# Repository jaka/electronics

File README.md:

# KiCad electronic projects repository

I like to solder, but information I find are scattered everywhere or incomplete. Here I collect schematics and PCBs.

Most of schematics came from datasheets or application notes. All PCBs were drawn by me.

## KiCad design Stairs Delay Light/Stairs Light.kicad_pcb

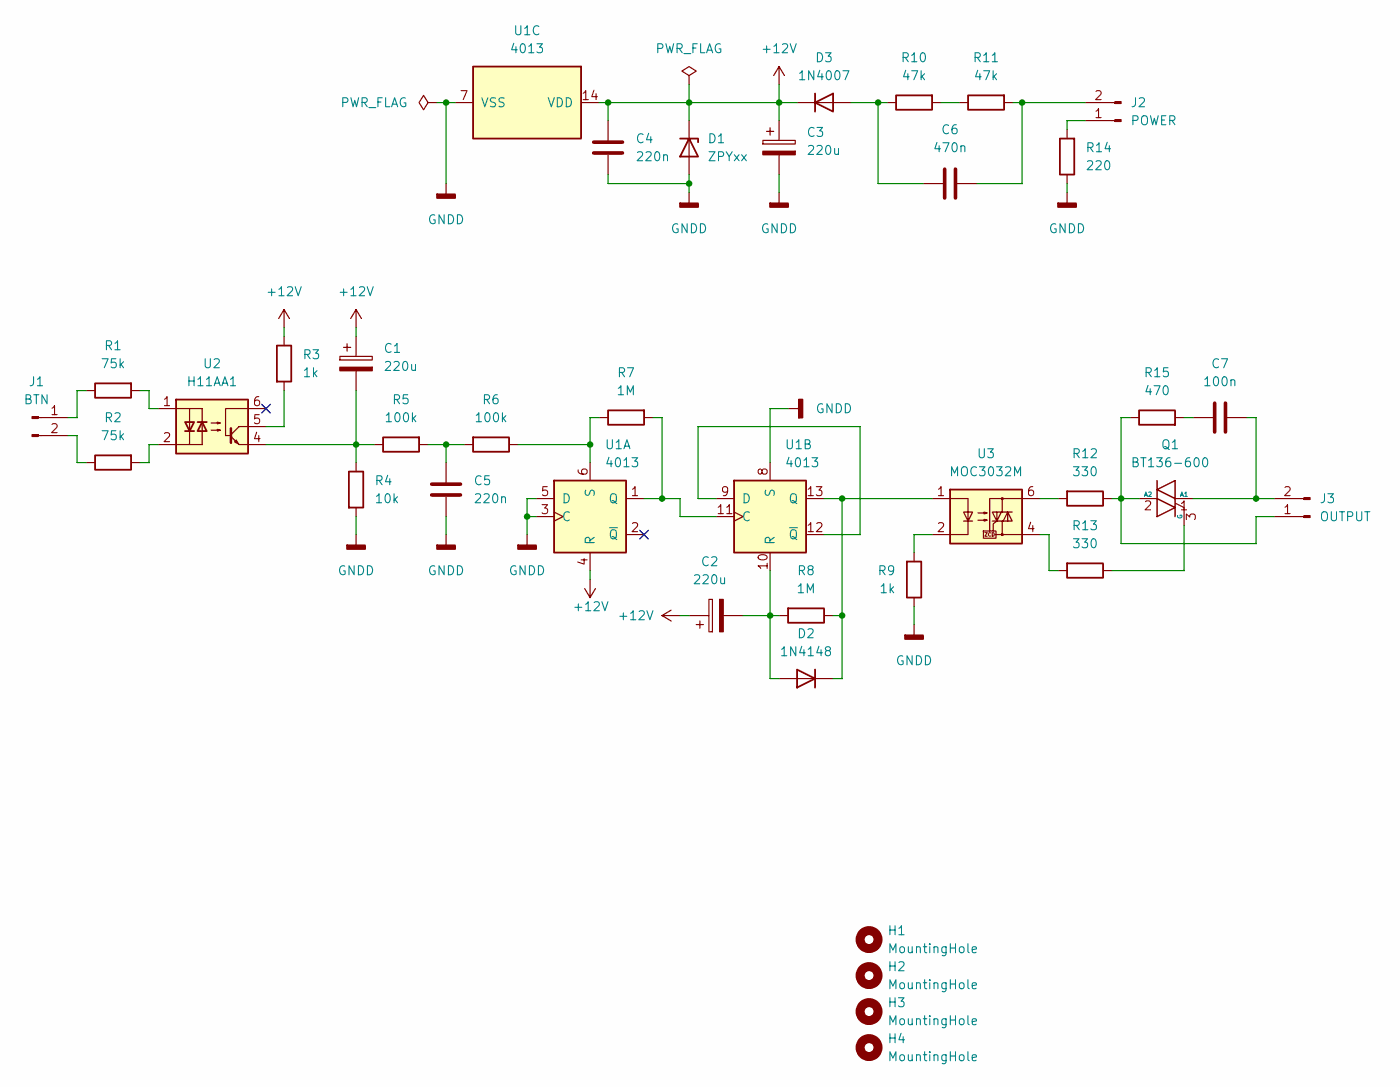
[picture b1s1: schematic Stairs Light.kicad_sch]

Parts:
C1, C2, C3: 220u; CP_Radial_D8.0mm_P3.50mm
C4, C5: 220n; C_Rect_L7.0mm_W3.5mm_P2.50mm_P5.00mm
C6: 470n; C_Rect_L24.0mm_W7.0mm_P22.50mm_MKT
C7: 100n; C_Rect_L24.0mm_W7.0mm_P22.50mm_MKT
D1: ZPYxx; D_DO-41_SOD81_P10.16mm_Horizontal
D2: 1N4148; D_DO-35_SOD27_P7.62mm_Horizontal
D3: 1N4007; D_DO-41_SOD81_P10.16mm_Horizontal
H1, H2, H3, H4: MountingHole; MountingHole_4.3mm_M4
J1: BTN; PhoenixContact_MSTBA_2,5_2-G-5,08_1x02_P5.08mm_Horizontal
J2: POWER; PhoenixContact_MSTBA_2,5_2-G-5,08_1x02_P5.08mm_Horizontal
J3: OUTPUT; PhoenixContact_MSTBA_2,5_2-G-5,08_1x02_P5.08mm_Horizontal
Q1: BT136-600; TO-220-3_Vertical
R1, R2: 75k; R_Axial_DIN0207_L6.3mm_D2.5mm_P10.16mm_Horizontal
R3, R9: 1k; R_Axial_DIN0207_L6.3mm_D2.5mm_P10.16mm_Horizontal
R4: 10k; R_Axial_DIN0207_L6.3mm_D2.5mm_P10.16mm_Horizontal
R5, R6: 100k; R_Axial_DIN0207_L6.3mm_D2.5mm_P10.16mm_Horizontal
R7, R8: 1M; R_Axial_DIN0207_L6.3mm_D2.5mm_P10.16mm_Horizontal
R10, R11: 47k; R_Axial_DIN0207_L6.3mm_D2.5mm_P10.16mm_Horizontal
R12, R13: 330; R_Axial_DIN0207_L6.3mm_D2.5mm_P10.16mm_Horizontal
R14: 220; R_Axial_DIN0309_L9.0mm_D3.2mm_P12.70mm_Horizontal
R15: 470; R_Axial_DIN0309_L9.0mm_D3.2mm_P12.70mm_Horizontal
U1: 4013; DIP-14_W7.62mm_Socket
U2: H11AA1; DIP-6_W7.62mm_LongPads
U3: MOC3032M; DIP-6_W7.62mm_LongPads

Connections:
+12V: C1.1, C2.1, C3.1, C4.1, D1.1 (K), D3.1 (K), R3.1, U1.4 (R), U1.14 (VDD)
GNDD: C3.2, C4.2, C5.2, D1.2 (A), R4.2, R9.1, R14.1, U1.3 (C), U1.5 (D), U1.7 (VSS), U1.8 (S)
unnamed: C1.2, R4.1, R5.1, U2.4
unnamed: C2.2, D2.2 (A), R8.2, U1.10 (R)
unnamed: C5.1, R5.2, R6.2
unnamed: C6.1, D3.2 (A), R10.1
unnamed: C6.2, J2.2, R11.2
unnamed: C7.1, J3.2, Q1.1 (A1)
unnamed: C7.2, R15.2
unnamed: D2.1 (K), R8.1, U1.13 (Q), U3.1
unnamed: J1.1, R1.1
unnamed: J1.2, R2.1
unnamed: J2.1, R14.2
unnamed: J3.1, Q1.2 (A2), R12.1, R15.1
unnamed: Q1.3 (G), R13.1
unnamed: R1.2, U2.1
unnamed: R2.2, U2.2
unnamed: R3.2, U2.5
unnamed: R6.1, R7.1, U1.6 (S)
unnamed: R7.2, U1.1 (Q), U1.11 (C)
unnamed: R9.2, U3.2
unnamed: R10.2, R11.1
unnamed: R12.2, U3.6
unnamed: R13.2, U3.4
unnamed: U1.9 (D), U1.12 (~Q)

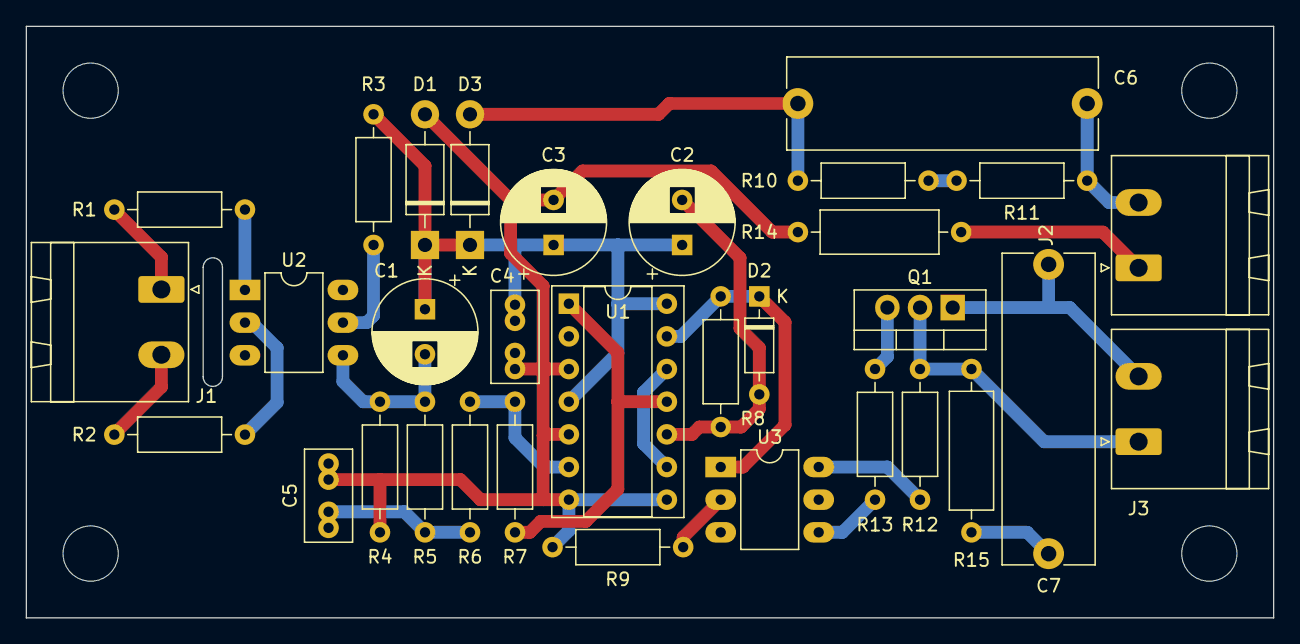
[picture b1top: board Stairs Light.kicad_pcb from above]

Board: 2 copper layers, 97.0 x 46.0 mm, 36 parts (0 on the bottom side), 25 nets.

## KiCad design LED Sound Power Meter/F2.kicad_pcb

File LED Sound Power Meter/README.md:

# LED Sound Power Meter

* EDA: **Kicad 6.0.11**
* PCB dimensions: **100 x 35 mm** (single sided)

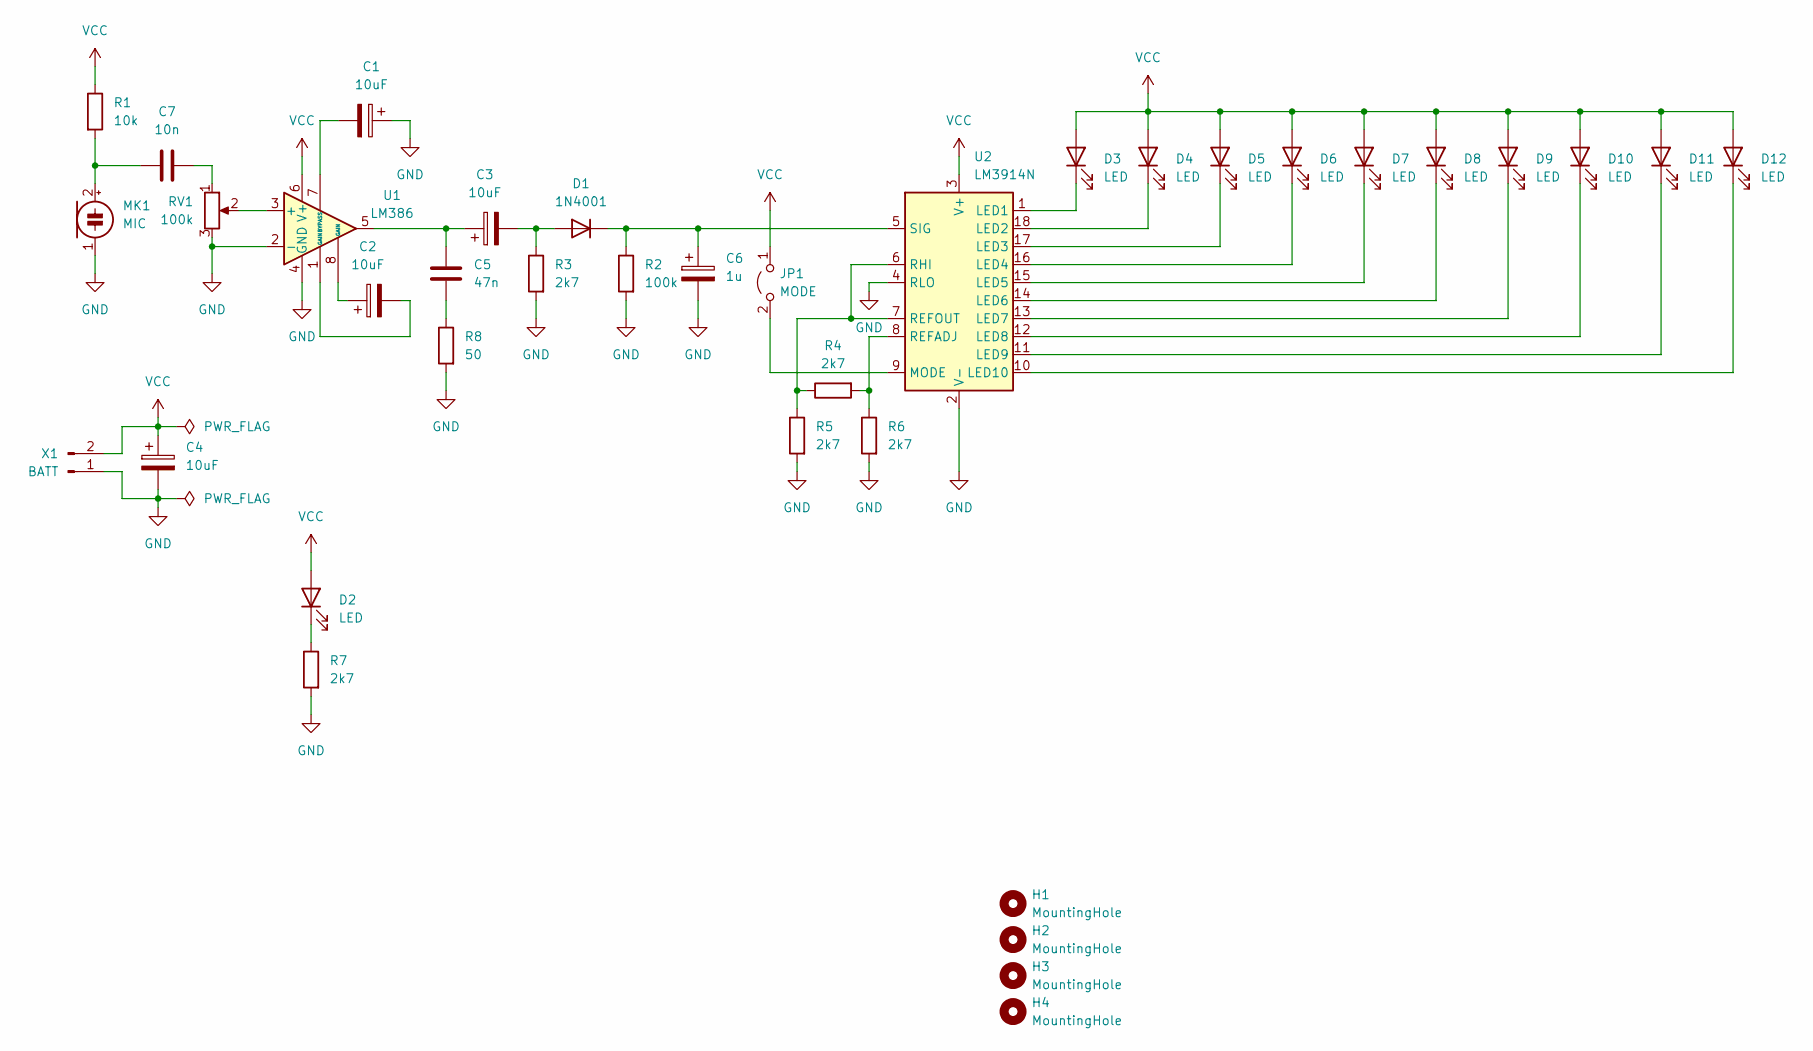
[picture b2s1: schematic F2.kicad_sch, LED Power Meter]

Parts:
C1, C2, C3, C4: 10uF; CP_Radial_D5.0mm_P2.00mm
C5: 47n; C_Rect_L7.0mm_W3.5mm_P2.50mm_P5.00mm
C6: 1u; CP_Radial_D5.0mm_P2.00mm
C7: 10n; C_Rect_L7.0mm_W3.5mm_P2.50mm_P5.00mm
D1: 1N4001; D_DO-41_SOD81_P10.16mm_Horizontal
D2, D3, D4, D5, D6, D7, D8, D9, D10, D11, D12: LED; LED_D5.0mm
H1, H2, H3, H4: MountingHole; MountingHole_3.2mm_M3
JP1: MODE; PinHeader_1x02_P2.54mm_Vertical
MK1: MIC; GMI9745P
R1: 10k; R_Axial_DIN0309_L9.0mm_D3.2mm_P12.70mm_Horizontal
R2: 100k; R_Axial_DIN0309_L9.0mm_D3.2mm_P12.70mm_Horizontal
R3, R4, R5, R6, R7: 2k7; R_Axial_DIN0309_L9.0mm_D3.2mm_P12.70mm_Horizontal
R8: 50; R_Axial_DIN0309_L9.0mm_D3.2mm_P12.70mm_Horizontal
RV1: 100k; Potentiometer_Piher_PT-10-V10_Vertical_Hole
U1: LM386; DIP-8_W7.62mm_LongPads
U2: LM3914N; DIP-18_W7.62mm_LongPads
X1: BATT; JST_PH_B2B-PH-K_1x02_P2.00mm_Vertical

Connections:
GND: C1.1, C4.2, C6.2, MK1.1 (-), R2.2, R3.2, R5.2, R6.2, R7.2, R8.2, RV1.3, U1.2 (-), U1.4 (GND), U2.2 (V-), U2.4 (RLO), X1.1
unnamed: C1.2, U1.7 (BYPASS)
unnamed: C2.1, U1.8 (GAIN)
unnamed: C2.2, U1.1 (GAIN)
unnamed: C3.1, C5.1, U1.5
unnamed: C3.2, D1.2 (A), R3.1
unnamed: C5.2, R8.1
unnamed: C6.1, D1.1 (K), R2.1, U2.5 (SIG)
unnamed: C7.1, MK1.2 (+), R1.2
unnamed: C7.2, RV1.1
unnamed: D2.1 (K), R7.1
unnamed: D3.1 (K), U2.1 (LED1)
unnamed: D4.1 (K), U2.18 (LED2)
unnamed: D5.1 (K), U2.17 (LED3)
unnamed: D6.1 (K), U2.16 (LED4)
unnamed: D7.1 (K), U2.15 (LED5)
unnamed: D8.1 (K), U2.14 (LED6)
unnamed: D9.1 (K), U2.13 (LED7)
unnamed: D10.1 (K), U2.12 (LED8)
unnamed: D11.1 (K), U2.11 (LED9)
unnamed: D12.1 (K), U2.10 (LED10)
unnamed: JP1.2 (B), U2.9 (MODE)
unnamed: R4.1, R5.1, U2.6 (RHI), U2.7 (REFOUT)
unnamed: R4.2, R6.1, U2.8 (REFADJ)
unnamed: RV1.2, U1.3 (+)
VCC: C4.1, D2.2 (A), D3.2 (A), D4.2 (A), D5.2 (A), D6.2 (A), D7.2 (A), D8.2 (A), D9.2 (A), D10.2 (A), D11.2 (A), D12.2 (A), JP1.1 (A), R1.1, U1.6 (V+), U2.3 (V+), X1.2

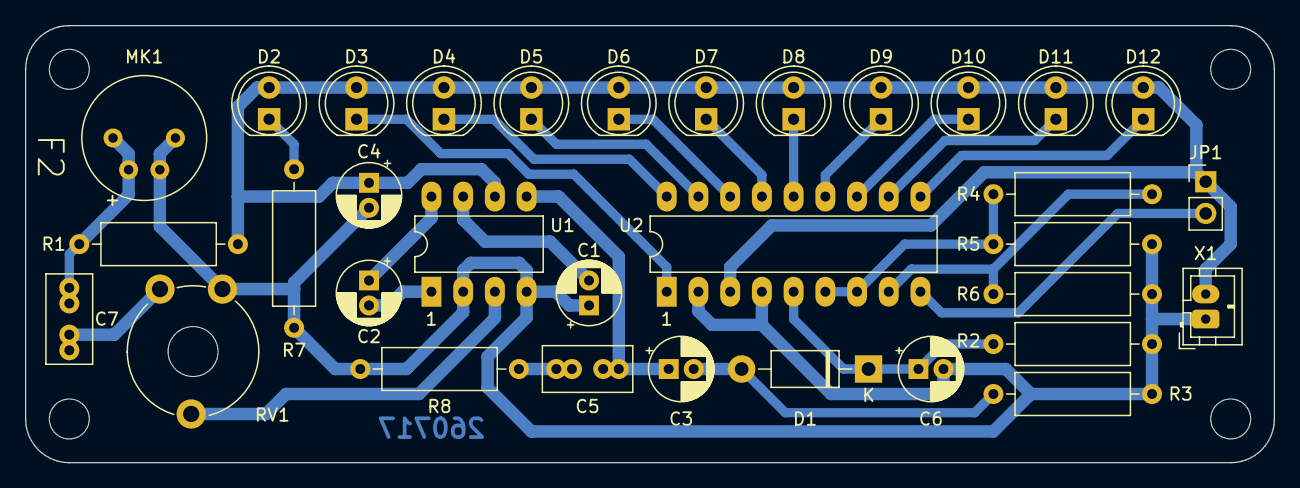
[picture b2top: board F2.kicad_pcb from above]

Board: 2 copper layers, 100.0 x 35.0 mm, 37 parts (0 on the bottom side), 26 nets.

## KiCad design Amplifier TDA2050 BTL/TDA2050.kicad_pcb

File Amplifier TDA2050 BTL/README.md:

# TDA2050 DIY Audio Power Amplifier Circuit

This is circuit combines two TDA2050 audio amplifier integrated circuits for so-called bridge-tied load where each speaker input is connected to amplifier output. Dual voltage power supply is needed.

* EDA: **Kicad 6.0.11**
* PCB dimensions: **74 x 39 mm** (single sided)

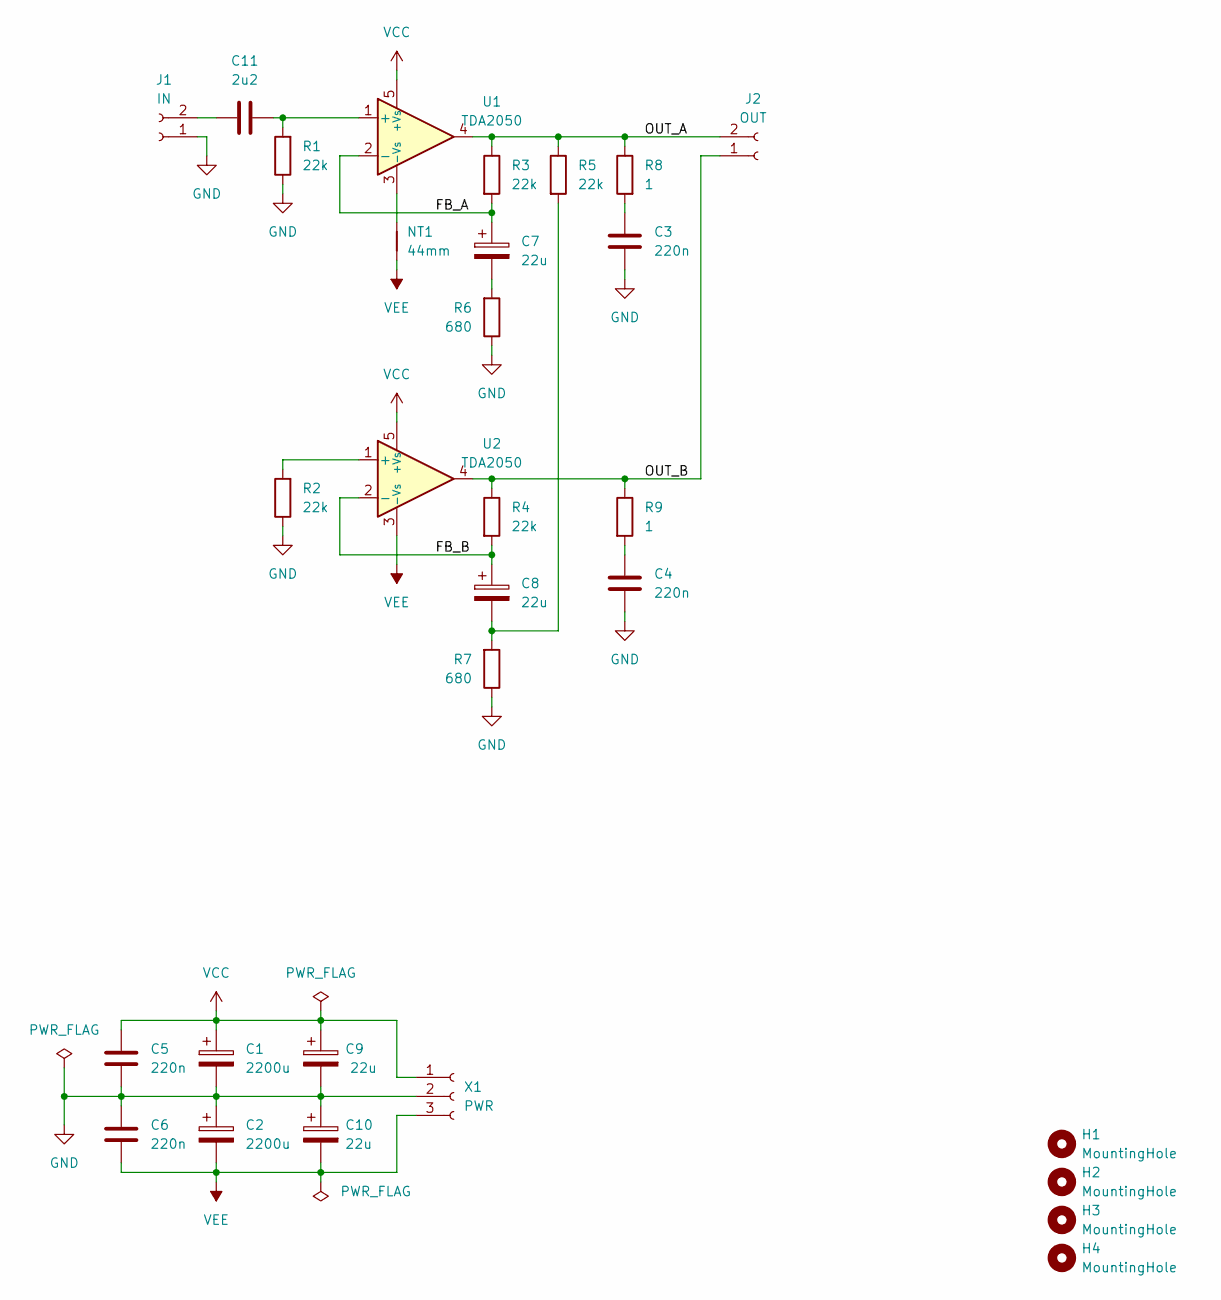
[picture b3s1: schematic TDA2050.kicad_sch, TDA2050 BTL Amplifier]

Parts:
C1, C2: 2200u; CP_Radial_D10.0mm_P5.00mm_P7.50mm
C3, C4, C5, C6: 220n; C_Rect_L7.0mm_W3.5mm_P2.50mm_P5.00mm
C7, C8, C9, C10: 22u; CP_Radial_D6.3mm_P2.50mm
C11: 2u2; C_Radial_D5.0mm_H7.0mm_P2.00mm
H1, H2, H3, H4: MountingHole; MountingHole_4.3mm_M4
J1: IN; JST_PH_B2B-PH-K_1x02_P2.00mm_Vertical
J2: OUT; JST_VH_B2P-VH_1x02_P3.96mm_Vertical
NT1: 44mm; Wire44mm
R1, R2, R3, R4, R5: 22k; R_Axial_DIN0207_L6.3mm_D2.5mm_P10.16mm_Horizontal
R6, R7: 680; R_Axial_DIN0207_L6.3mm_D2.5mm_P10.16mm_Horizontal
R8, R9: 1; R_Axial_DIN0309_L9.0mm_D3.2mm_P5.08mm_Vertical
U1, U2: TDA2050; TO-220-5_P3.4x3.7mm_StaggerOdd_Lead3.8mm_Vertical
X1: PWR; JST_VH_B3P-VH_1x03_P3.96mm_Vertical

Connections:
/FB_A: C7.1, R3.2, U1.2 (-)
/FB_B: C8.1, R4.2, U2.2 (-)
/OUT_A: J2.2, R3.1, R5.1, R8.1, U1.4
/OUT_B: J2.1, R4.1, R9.1, U2.4
GND: C1.2, C2.1, C3.2, C4.2, C5.2, C6.1, C9.2, C10.1, J1.1, R1.1, R2.1, R6.1, R7.1, X1.2
unnamed: C7.2, R6.2
unnamed: C8.2, R5.2, R7.2
unnamed: C11.1, J1.2
unnamed: C11.2, R1.2, U1.1 (+)
unnamed: R2.2, U2.1 (+)
unnamed: C3.1, R8.2
unnamed: C4.1, R9.2
unnamed: NT1.2, U1.3 (-Vs)
VCC: C1.1, C5.1, C9.1, U1.5 (+Vs), U2.5 (+Vs), X1.1
VEE: C2.2, C6.2, C10.2, NT1.1, U2.3 (-Vs), X1.3

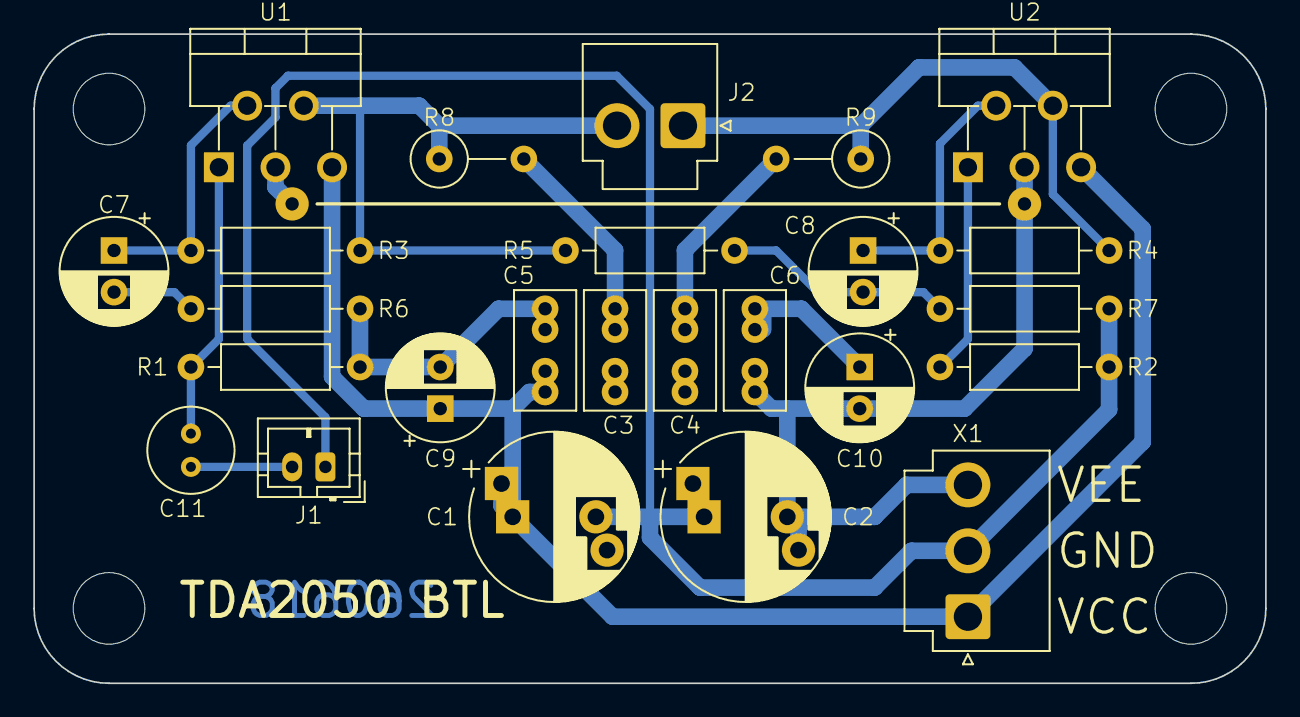
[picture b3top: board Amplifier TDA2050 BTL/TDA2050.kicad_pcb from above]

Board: 2 copper layers, 74.0 x 39.0 mm, 30 parts (0 on the bottom side), 15 nets.

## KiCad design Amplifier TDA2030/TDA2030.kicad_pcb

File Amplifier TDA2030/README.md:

# TDA2030 DIY Audio Power Amplifier Circuit

This is a simple class AB audio amplifier built around the TDA2030 audio amplifier integrated circuit. It’s a classic beginner-friendly design often used for small speakers, desktop audio, or homemade powered speakers, where only one power supply voltage is available.

* EDA: **Kicad 6.0.11**
* PCB dimensions: **61 x 34 mm** (single sided)

Circuit is versatile: it can also accomodate TDA2030A, TDA2050 and LM1875 due to same pinout, but in all cases heat sink for IC is mandatory!

# Expected performance

| Supply Voltage | Speaker | Approx. Power |
|---|---|---|
| 12V | 8Ω | 6–8W |
| 18V | 4Ω | 14–18W |

## Power supply
- 12 V–18 V regulated DC supply
- 2 A or more

## When built

Before connecting the loudspeaker and input source, measure (bias) voltage at test point TP1. The voltage here should be a half of supply voltage. If it's not, check both resistors R₁ and R₂ or replace C₁. Capacitor may have too low resistance and some current is flowing through, resulting in bias voltage drop. The same voltage should be at test point TP2 just before output DC decoupling capacitor.

| Component | Recommended value | Purpose | Larger than recommended value | Smaller than recommended value |
|-----------|------------------|---------|------------------------------|-------------------------------|
| R₁/R₂ | 100 kΩ | Bias voltage divider | Poor high-frequency attenuation | Danger of oscillation |
| R₃ | 100 kΩ | Non-inverting input biasing | Increase of input impedance | Decrease in input impedance |
| R₄ | 4,7kΩ | Closed loop gain setting | Decrease of gain | Increase in gain |
| R₅ | 100 kΩ | Closed loop gain setting | Increase of gain | Decrease in gain |
| R₆ | 1 Ω | Frequency stability | Danger of oscillation at high frequencies with inductive loads | — |
| R₇ | 2 kΩ | Upper frequency cutoff | Poor high-frequency attenuation | — |
| C₁ | 10 µF | Bias voltage stabilizing | | |
| C₂ | 2,2 µF | Input DC decoupling | — | Increase in low-frequency cutoff |
| C₃ | 2,2 µF | Inverting input DC decoupling | — | Increase in low-frequency cutoff |
| C₄ | 220 µF | Supply voltage bypass | — | Danger of oscillation |
| C₅ | 0,22 µF | Supply voltage bypass | — | Danger of oscillation |
| C₆ | 0,22 µF | Frequency stability | — | Danger of oscillation |
| C₇ | 1 / (2πBR₅) | Upper frequency cutoff | Smaller bandwidth | Larger bandwidth |
| C₈ | 2200 µF | Output DC decoupling | — | Increase in low-frequency cutoff |
| D₁, D₂ | 1N4001 | To protect the device against output voltage spikes | — | — |

These values are from ST TDA2030A datasheet. ST does not produce this IC anymore, but there are many others producers. Check theirs datasheet for recommended values.

Closed loop gain must be higher than 24 dB.

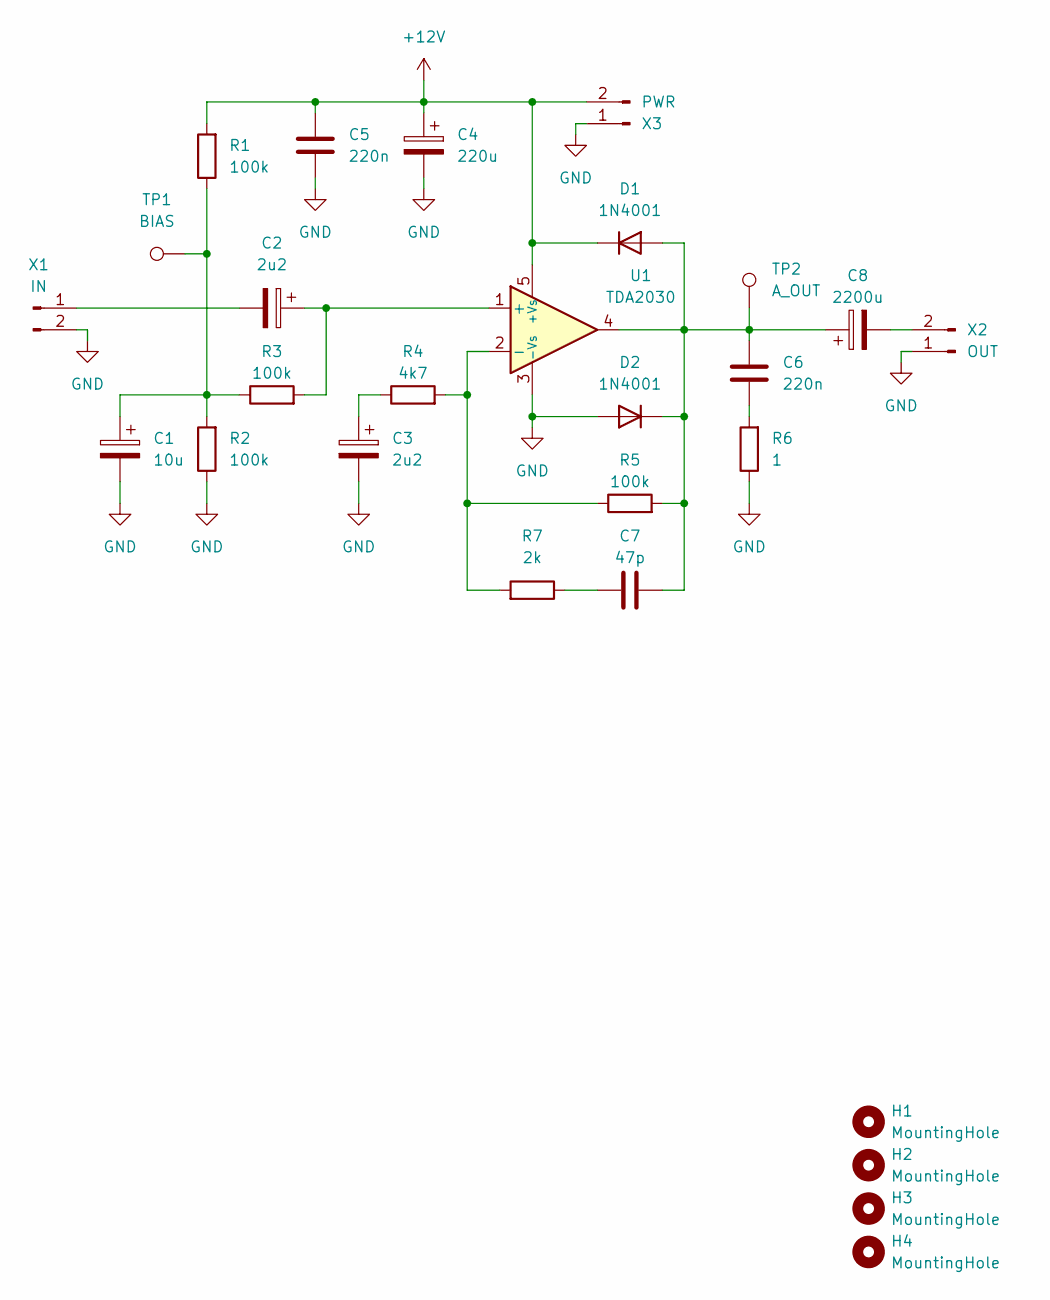
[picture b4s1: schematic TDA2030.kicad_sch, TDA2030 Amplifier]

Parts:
C1: 10u; CP_Radial_D5.0mm_P2.50mm
C2, C3: 2u2; CP_Radial_D5.0mm_P2.50mm
C4: 220u; CP_Radial_D10.0mm_P2.50mm_P5.00mm
C5, C6: 220n; C_Rect_L7.0mm_W3.5mm_P2.50mm_P5.00mm
C7: 47p; C_Rect_L7.0mm_W3.5mm_P2.50mm_P5.00mm
C8: 2200u; CP_Radial_D10.0mm_P5.00mm_P7.50mm
D1, D2: 1N4001; D_DO-41_SOD81_P10.16mm_Horizontal
H1, H2, H3, H4: MountingHole; MountingHole_3.2mm_M3
R1, R2, R3, R5: 100k; R_Axial_DIN0309_L9.0mm_D3.2mm_P12.70mm_Horizontal
R4: 4k7; R_Axial_DIN0309_L9.0mm_D3.2mm_P12.70mm_Horizontal
R6: 1; R_Axial_DIN0411_L9.9mm_D3.6mm_P5.08mm_Vertical
R7: 2k; R_Axial_DIN0309_L9.0mm_D3.2mm_P12.70mm_Horizontal
TP1: BIAS; TestPoint_Pad_D2.5mm
TP2: A_OUT; TestPoint_Pad_D2.5mm
U1: TDA2030; TO-220-5_P3.4x3.7mm_StaggerOdd_Lead3.8mm_Vertical
X1: IN; JST_PH_B2B-PH-K_1x02_P2.00mm_Vertical
X2: OUT; JST_VH_B2P-VH-B_1x02_P3.96mm_Vertical
X3: PWR; JST_VH_B2P-VH-B_1x02_P3.96mm_Vertical

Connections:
+12V: C4.1, C5.1, D1.1 (K), R1.2, U1.5 (+Vs), X3.2
GND: C1.2, C3.2, C4.2, C5.2, D2.2 (A), R2.1, R6.1, U1.3 (-Vs), X1.2, X2.1, X3.1
unnamed: C1.1, R1.1, R2.2, R3.1, TP1.1
unnamed: C2.1, R3.2, U1.1 (+)
unnamed: C2.2, X1.1
unnamed: C3.1, R4.1
unnamed: C6.1, C7.2, C8.1, D1.2 (A), D2.1 (K), R5.2, TP2.1, U1.4
unnamed: C6.2, R6.2
unnamed: C7.1, R7.1
unnamed: C8.2, X2.2
unnamed: R4.2, R5.1, R7.2, U1.2 (-)

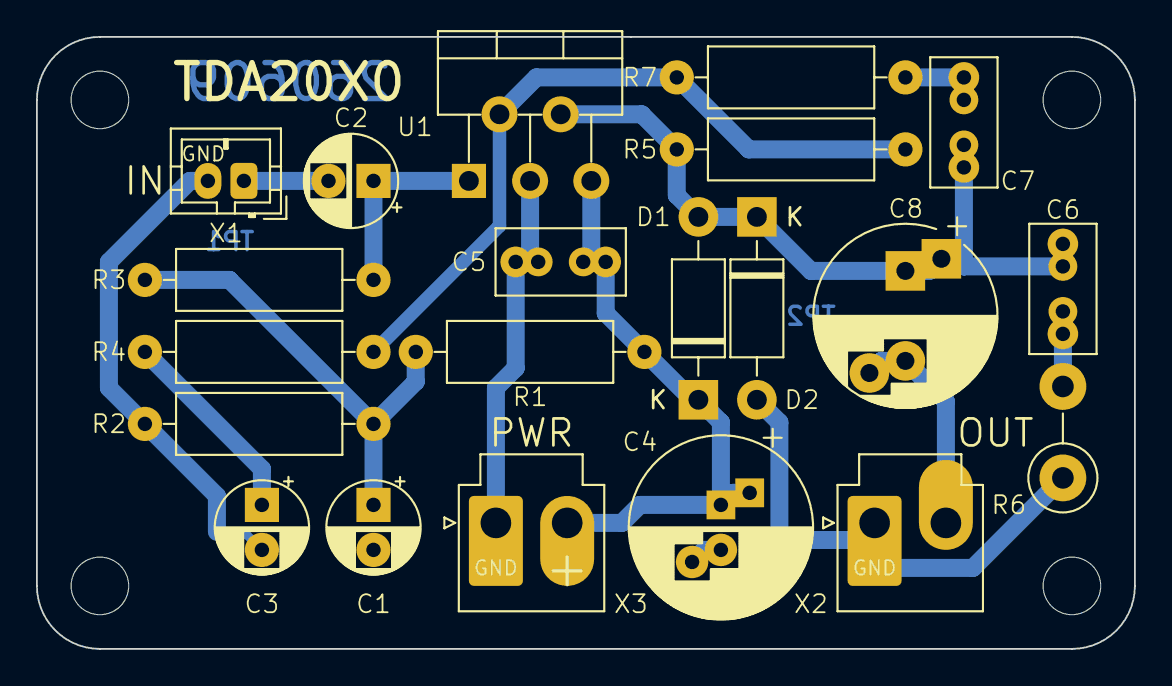
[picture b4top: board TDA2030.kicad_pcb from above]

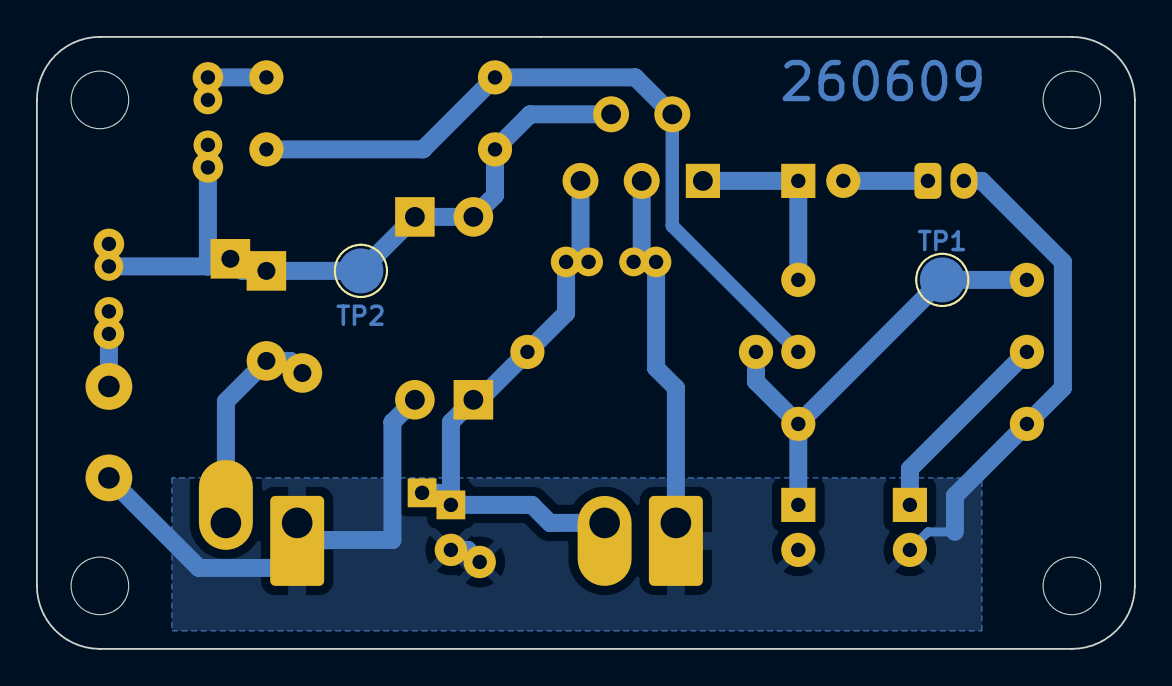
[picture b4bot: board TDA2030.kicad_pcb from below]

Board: 2 copper layers, 61.0 x 34.0 mm, 27 parts (2 on the bottom side), 11 nets.

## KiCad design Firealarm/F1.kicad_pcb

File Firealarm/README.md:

# Firealarm Tone Generator

This circuit simulates a fire alarm sound. When button SW1 is pressed, loudspeaker connected to terminal LS1 emits a tone that gradually rises in pitch and then holds steady at a constant pitch. The tone continues until the button is released. The pitch then drops again until the sound ceases completely. This process can be repeated indefinitely.

* EDA: **Kicad 6.0.11**
* PCB dimensions: **58 x 36 mm** (single sided)

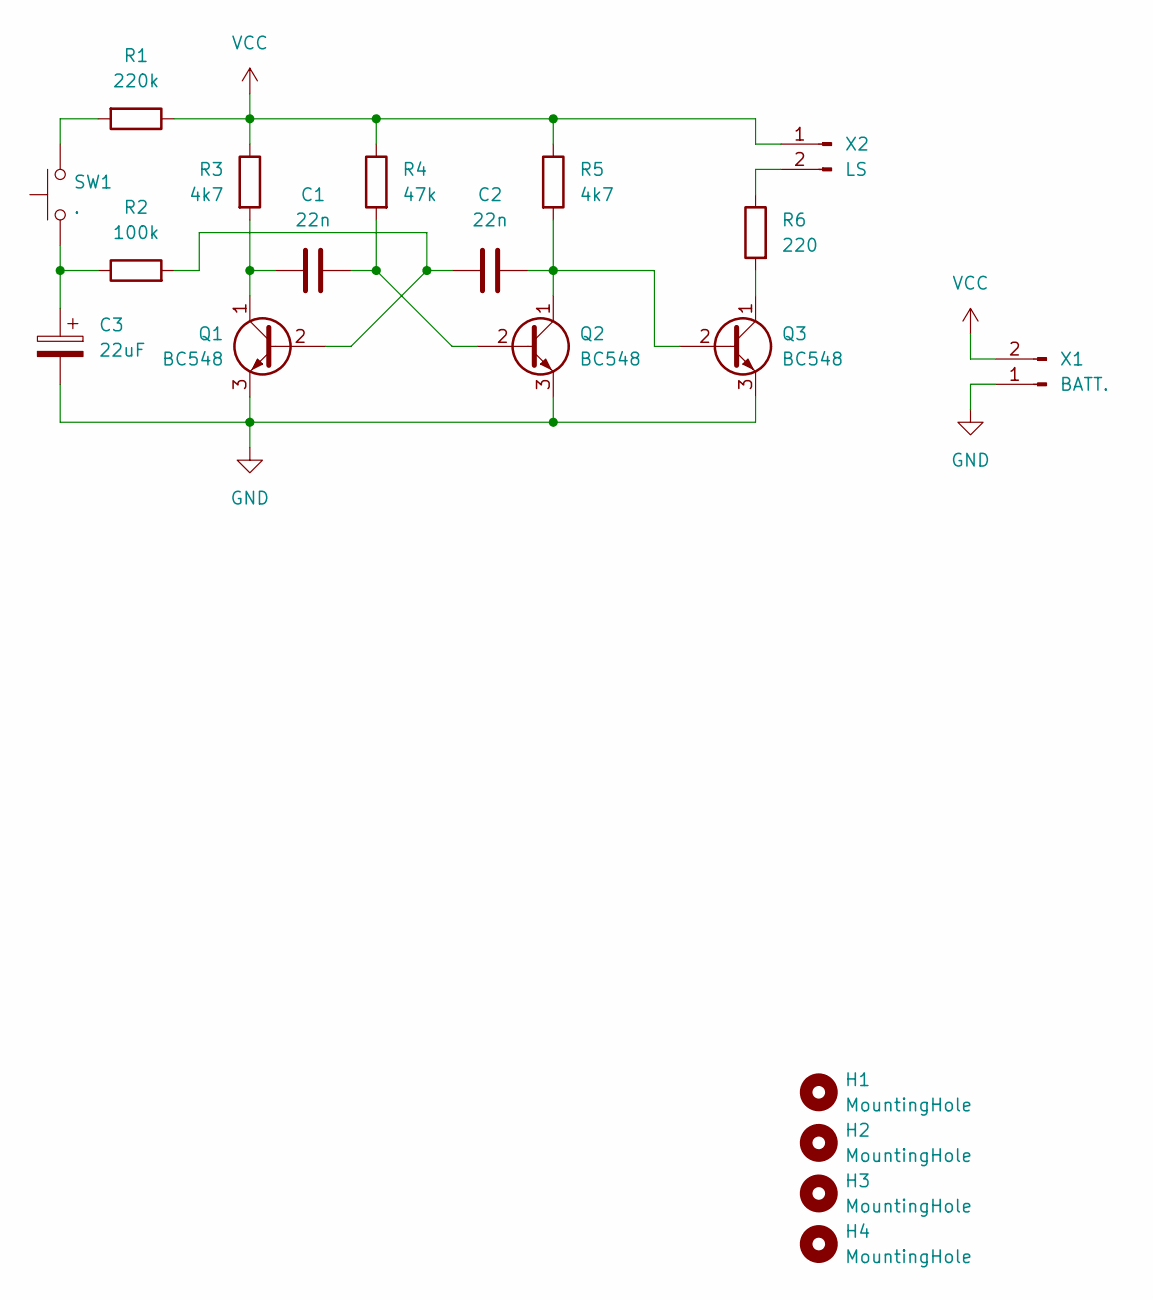
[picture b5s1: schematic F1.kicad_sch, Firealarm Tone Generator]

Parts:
C1, C2: 22n; C_Disc_D5.0mm_W2.5mm_P5.00mm
C3: 22uF; CP_Radial_D5.0mm_P2.50mm
H1, H2, H3, H4: MountingHole; MountingHole_3.5mm
Q1, Q2, Q3: BC548; TO-92_Inline_Wide
R1: 220k; R_Axial_DIN0207_L6.3mm_D2.5mm_P10.16mm_Horizontal
R2: 100k; R_Axial_DIN0207_L6.3mm_D2.5mm_P10.16mm_Horizontal
R3, R5: 4k7; R_Axial_DIN0207_L6.3mm_D2.5mm_P10.16mm_Horizontal
R4: 47k; R_Axial_DIN0207_L6.3mm_D2.5mm_P10.16mm_Horizontal
R6: 220; R_Axial_DIN0207_L6.3mm_D2.5mm_P10.16mm_Horizontal
SW1: .; SW_PUSH_6mm
X1: BATT.; JST_PH_B2B-PH-K_1x02_P2.00mm_Vertical
X2: LS; Molex_KK-254_AE-6410-02A_1x02_P2.54mm_Vertical

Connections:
GND: C3.2, Q1.3 (E), Q2.3 (E), Q3.3 (E), X1.1
unnamed: C1.1, Q1.1 (C), R3.2
unnamed: C1.2, Q2.2 (B), R4.2
unnamed: C2.1, Q1.2 (B), R2.2
unnamed: C2.2, Q2.1 (C), Q3.2 (B), R5.2
unnamed: C3.1, R2.1, SW1.1
unnamed: Q3.1 (C), R6.2
unnamed: R1.2, SW1.2
unnamed: R6.1, X2.2
VCC: R1.1, R3.1, R4.1, R5.1, X1.2, X2.1

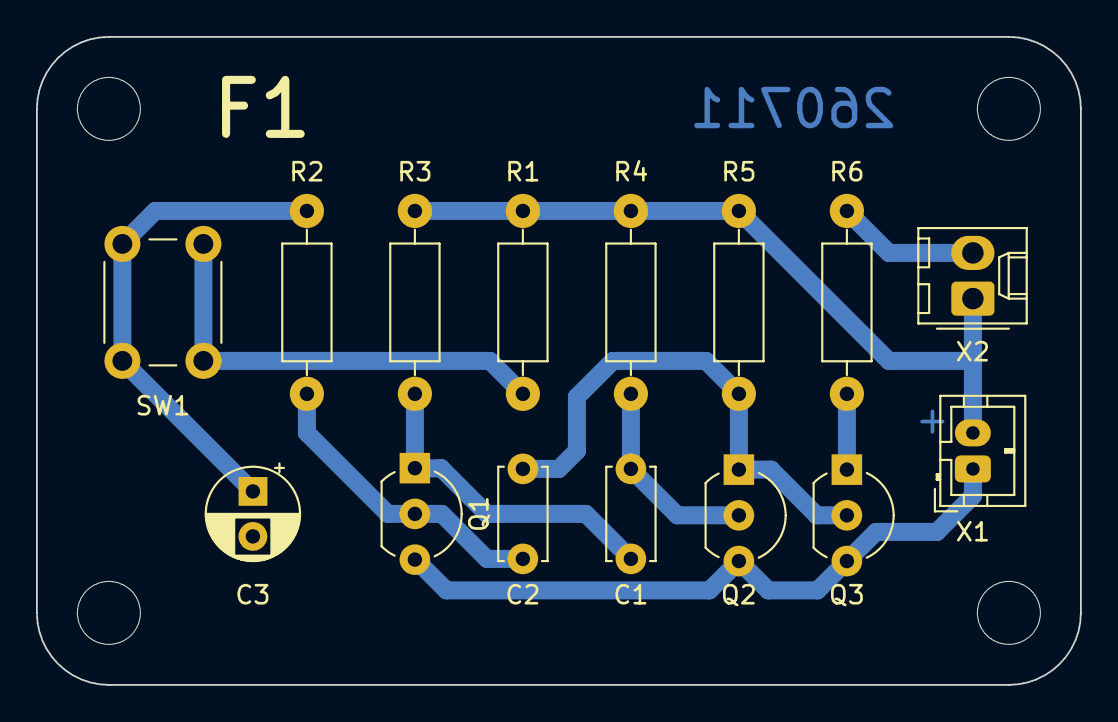
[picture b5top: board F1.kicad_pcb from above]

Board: 2 copper layers, 58.0 x 36.0 mm, 19 parts (0 on the bottom side), 10 nets.

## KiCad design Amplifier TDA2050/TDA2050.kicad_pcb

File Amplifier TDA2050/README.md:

# TDA2050 DIY Audio Power Amplifier Circuit

This is a simple amplifier based on IC datasheet. Dual voltage power supply is needed.

* EDA: **Kicad 6.0.11**
* PCB dimensions: **54 x 39 mm** (single sided)

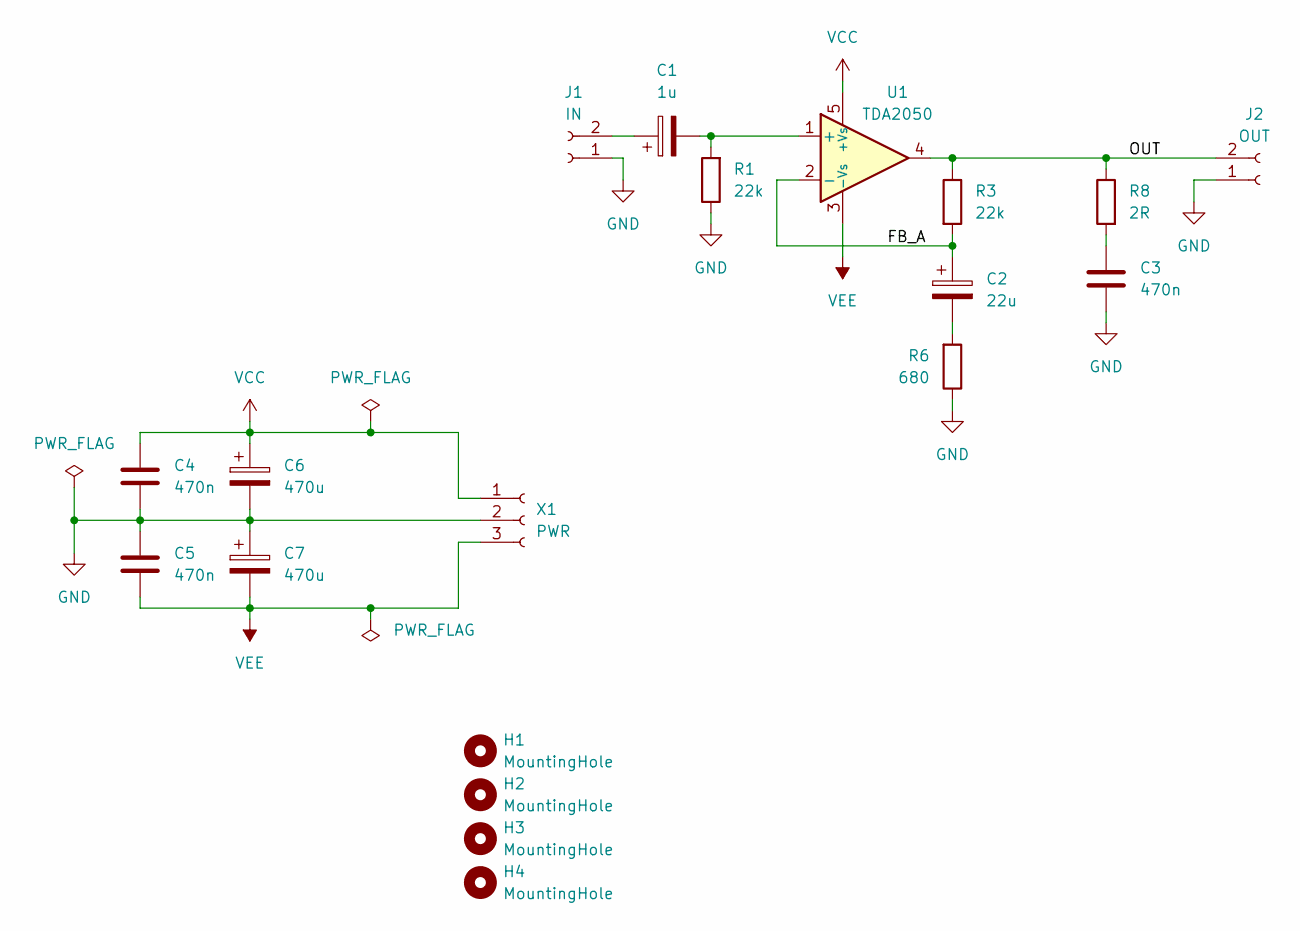
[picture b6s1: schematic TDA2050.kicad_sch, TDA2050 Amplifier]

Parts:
C1: 1u; CP_Radial_D5.0mm_P2.00mm
C2: 22u; CP_Radial_D6.3mm_P2.50mm
C3, C4, C5: 470n; C_Rect_L7.0mm_W3.5mm_P2.50mm_P5.00mm
C6, C7: 470u; CP_Radial_D10.0mm_P5.00mm_P7.50mm
H1, H2, H3, H4: MountingHole; MountingHole_4.3mm_M4
J1: IN; JST_PH_B2B-PH-K_1x02_P2.00mm_Vertical
J2: OUT; JST_VH_B2P-VH_1x02_P3.96mm_Vertical
R1, R3: 22k; R_Axial_DIN0207_L6.3mm_D2.5mm_P10.16mm_Horizontal
R6: 680; R_Axial_DIN0207_L6.3mm_D2.5mm_P10.16mm_Horizontal
R8: 2R; R_Axial_DIN0309_L9.0mm_D3.2mm_P5.08mm_Vertical
U1: TDA2050; TO-220-5_P3.4x3.7mm_StaggerOdd_Lead3.8mm_Vertical
X1: PWR; JST_VH_B3P-VH_1x03_P3.96mm_Vertical

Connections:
/FB_A: C2.1, R3.2, U1.2 (-)
/OUT: J2.2, R3.1, R8.1, U1.4
GND: C3.2, C4.2, C5.1, C6.2, C7.1, J1.1, J2.1, R1.1, R6.1, X1.2
unnamed: C1.1, J1.2
unnamed: C1.2, R1.2, U1.1 (+)
unnamed: C2.2, R6.2
unnamed: C3.1, R8.2
VCC: C4.1, C6.1, U1.5 (+Vs), X1.1
VEE: C5.2, C7.2, U1.3 (-Vs), X1.3

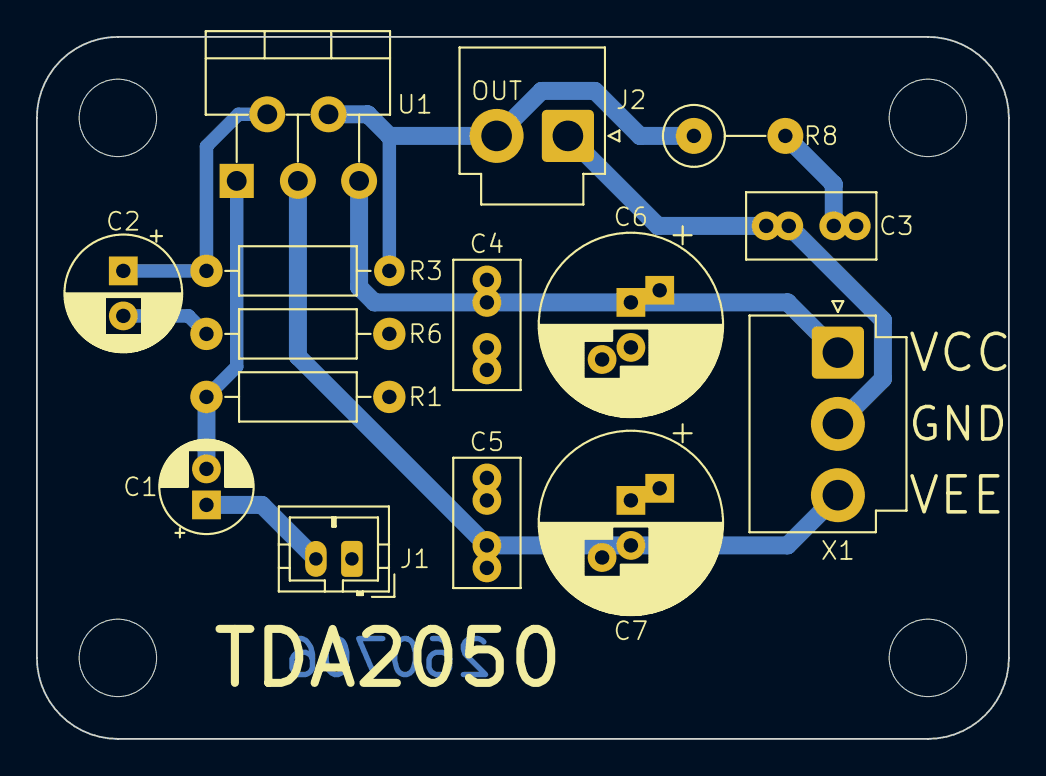
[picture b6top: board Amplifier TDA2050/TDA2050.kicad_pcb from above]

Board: 2 copper layers, 54.0 x 39.0 mm, 19 parts (0 on the bottom side), 9 nets.
